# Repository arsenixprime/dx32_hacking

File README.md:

This project is focused on reverse engineering the Bridgeport DX32 CNC controller. This system uses a DOS based PC, running a custom CNC user interface applicaiton. It has an ISA card in it called the "BMDC", which has a Motorolla 68k family microcontroller on it. This card talks to two other cards via RS422 serial ports, the AUF and the TCLAuf. The AUF is used for general purpose I/O control and the TCLAuf is used for driving tool change related I/O.

Binaries provided:
* B3T.EXE - A simple system test application that exercises the functions of the BMDC board.
* BXX.EXE - The primary DX32 user interface application
* BMDC.BIN - The BMDC binary firmware, loaded by B3T or BXX when they start.
* MAINTPG.EXE - Maintenance program for viewing real-time I/O status (AUF inputs/outputs, TLAUF inputs/outputs)
* MAINTPG1.DAT - Data file for MAINTPG.EXE containing parameter bit definitions for all status/command words

More information about the BMDC board hardware. The various devices are connected via a number of programmable PALs for which the circuit diagrams are unavailable so the address mapping is unknown. The components on the board are:
* MC68EC030FE40C - Primary CPU running the firmware
* MC68882FN25A - Math coprocessor
* MAX161ACPI
* 2x ADM5180JP
* SCN2681AC1A44 - Two port async serial port

The address map is unknown

The AUF Board has:
* MC68HC811E2FN - Microcontroller
** Does have an 8ch 8bit ADC
* 4 Bit Switches for Address Select (Default 0000)
* 2x LTC485 RS422 Driver Chips
* 24x Input Channels
* 8x 24V DC Outputs. 7x Low Side. 1x High Side.
* 4x AC Outputs
* 2x LEDs, D11 and D12

## Reverse Engineering Documentation

* [PROTOCOL_NOTES.md](PROTOCOL_NOTES.md) — Master protocol document. Serial protocol between BMDC, AUF, and TLAUF (UART configuration, packet formats), ISA I/O port map, dual-port RAM layout, 68030 memory map, the TLAUF TX command protocol (VMC vs non-VMC modes), the timer/interrupt schedule (4 ms servo tick), the boot-time RAM/dual-port sizing probe, the key firmware function table, and the complete PC→BMDC mailbox command table with the DOS-side names (doMove, armProbe, wrPartPgm, ...).
* [HOMING_SEQUENCE.md](HOMING_SEQUENCE.md) — How the carousel homes on startup. Traces the full call chain from drive-ready detection through the task dispatcher to the pocket-send protocol that commands the TLAUF to move to pocket 1.
* [TOOL_CHANGE_STATE_MACHINE.md](TOOL_CHANGE_STATE_MACHINE.md) — Non-VMC tool change step machine. Documents the outer state machine (subroutine call stack) and inner step machine (carousel seek, orient, rotate) that runs when the BMDC directly controls motor outputs.
* [AUF_PACKET_FORMAT.md](AUF_PACKET_FORMAT.md) — Detailed AUF packet encoding/decoding. Covers the nibble packing for short and long packets, input debounce logic, and output bit assignments.
* [MOTION_PLANNER.md](MOTION_PLANNER.md) — How the BMDC firmware plans motion. Firmware units (10 nm, 4 ms tick), the trapezoid vs S-curve velocity planners and what parameter 010 (accel/decel profile, values 0-5) changes, when the S-curve falls back to the trapezoid, G8/G9/G99 and the P (precision) word with the corner-blending classifier, how the F word is scaled and used in combined X/Y/Z/C moves (F after a C word is the C-axis rate in deg/min, caps from parameters 7/8/47), the G117/G118/G119 rotary-coordinated moves, the move-type dispatch table, and the touch-probe engine (PC-driven via mailbox; there are no G-code probing cycles).
* [BMDC_PARAM_TABLE.md](BMDC_PARAM_TABLE.md) — All 288 firmware parameter slots (number, 68030 address, data type, title) extracted from the firmware's parameter table at 0x2a536. Use it to find where a `BMDCPRMS.SYS` parameter lives in BMDC RAM.
* [BMDC_RAM_UPGRADE.md](BMDC_RAM_UPGRADE.md) — Adding main RAM to a BMDC3 for a larger part-program buffer (the "part program memory full" alarm). Documents the fitted SRAM (MCM6226BBXJ20, 4 × 128K×8 = 512 KB), its full pin assignment, the 300-mil and 400-mil SOJ package dimensions (pitch, lead span, land pattern), the 36-lead package used by 512K×8 parts, how the firmware sizes RAM at boot and why a stock BMDC3 halts above 512 KB, the two-byte firmware patch (`tools/patch_bmdc_ram.py`), the castellated-adapter plan for 2 MB, the ISA-window test for the address decoder, and the DNC alternative.
* [BMDC_RAM_INTERPOSER_PROMPT.md](BMDC_RAM_INTERPOSER_PROMPT.md) — Ready-to-use Claude Code prompt (kicad-happy skills, KiCad 10) for designing the castellated interposer PCB that puts a 36-lead SOJ 512K×8 SRAM (CY7C1049G-10VXI) on the BMDC3's 32-lead wide SOJ site: 4-layer stack with +5 V pour over a GND plane, four 0402 decoupling caps, the host and chip pinouts, the free address/data permutation that makes it routable, a suggested net map, jumpers for A17/A18, the pad-vs-castellation clearance arithmetic, the measurements to confirm on the card, and the deliverables checklist.
* [BMDCPRMS_INI.md](BMDCPRMS_INI.md) — What each line of `BMDCPRMS.INI` does: it is a per-model override table (machine model, spindle option, 10-inch rotary table) of parameter numbers and values for `BMDCPRMS.SYS`, with the firmware address and use of every parameter it touches (travel limits, Z and C traverse caps, spindle gear-range RPMs, C-axis gains). No program in the repo reads it; its consumer is unknown.
* [BMDC3_VS_BMDC4.md](BMDC3_VS_BMDC4.md) — Every board-class branch in the firmware: how the class is decided (CPU benchmark, 1 MB + 8 KB memory fit forces BMDC4), the 68030 vs 68040 cache and FPU-software-package setup, all boot halt codes (0x90, 0xa0-0xa8, 0xb0/0xb8, 0xc0-0xe0+n), the derived hardware constants, and the runtime differences (DAC width and count, spindle DAC location and scaling, 9 vs 6 encoders, mux ADC, 16-bit input port). Includes photos of a BMDC-4B with the PWMINT daughterboard fitted and of a BMDC3S rev C without it and the assessment of running a PWMINT TC22 on a BMDC4.
* [BMDC_AXIS_OUTPUTS.md](BMDC_AXIS_OUTPUTS.md) — How the firmware chooses between the on-board analog axis DACs and the PWMINT duty-cycle card: the boot signature probe and flag 0xafc4, the halt codes 0xa1/0xa2, the PWMINT register block, the servo-tick output path and what changes between modes (centre, clamp window, gain shift, default parameter block), the PWM clamp-window maths behind parameters 124-145, why the spindle DAC is always analog, the PWMINT status/fault checks, and what happens when the card is removed.
* [BMDC_PROBE_INTERNALS.md](BMDC_PROBE_INTERNALS.md) — How touch probing works across BXX and the firmware: the PROBE ON/OFF toggle (parameter 7 plus armProbe), the overlay PROBEPT primitive, the firmware probe cycle and position latch, how SET X computes and stores work zero (the four offset copies and per-block zeros), where tool changes pass through, and the loader behaviour. Research notes for auto probe-mode and auto-zero features; nothing implemented.
* [hardware/bmdc_ram_interposer/](hardware/bmdc_ram_interposer/README.md) — The interposer itself, rev A (KiCad 10): generated 4-layer castellated board (11.83 × 27.6 mm, 32 castellations at 1.27 mm, short-pad SOJ-36 on top, four 0402 caps, JP1/JP2 solder jumpers and A17/A18 wire pads), ERC/DRC/schematic-parity clean, with gerbers/drill/CPL/BOM for JLCPCB, 3D renders, STEP, datasheets and kicad-happy analyzer reports. Everything is regenerated from `tools/params.py`; the row pitch, host pad size, chip-to-chip pitch and end clearance are still nominal and must be measured on the card before ordering.

## Mechanical Parts

* [mechanical/](mechanical/README.md) — Printed/machined hardware for the retrofit, one CadQuery generator per part with a README stating what has actually been built. Currently: [yaskawa_cord_grip/](mechanical/yaskawa_cord_grip/README.md), a split clamshell cord grip for a 3/4" knockout that passes a 0.25" and a 0.375" cable with right-angle connectors on both ends (designed, not yet printed).

## Decompiled Sources

* `decompiled/BMDC.c`, `decompiled/BXX.c`, `decompiled/B3T.c`, `decompiled/MAINTPG.c` — Ghidra decompilation of each binary, one file per binary. Grep here first rather than re-running Ghidra. `B3T.c` has real function names from the CodeView symbols.
* `decompiled/BMDC.asm` — Full Ghidra disassembly listing of the firmware. Use it whenever a `BMDC.c` function is truncated: the decompiler cannot model the 68882 `FMOVECR` / packed-decimal instructions and silently drops everything after them.
* `decompiled/B3T_symbols.txt` — CodeView symbols from `B3T.EXE` (address, kind, name, source module). The DOS-side names of the mailbox commands come from here.
* `decompiled/B3T_types.txt` — CodeView struct/union/enum records from `B3T.EXE`: the MOVEBUFFER, MOVCMD, MOVFLGS, dualPortRAM, MCCMD and parameter-block layouts shared between the DOS software and the firmware.

## Tools and Scripts

* `tools/cv_nb09.py` — Parses the CodeView NB09 debug block at the end of `B3T.EXE` and prints the symbol table (source of `decompiled/B3T_symbols.txt`).
* `tools/cv_types.py` — Dumps CodeView type records (structs, bit fields) from `B3T.EXE` by type index (source of `decompiled/B3T_types.txt`).
* `tools/m68k_dis.py` — Capstone disassembler for `BMDC.BIN` (`python3 tools/m68k_dis.py START END`) with resync after undecodable words and decoded extended-precision immediates. Needed for the mailbox, G-code-letter and move-type handlers that Ghidra never disassembled because they are only reached through jump tables.
* `tools/patch_bmdc_ram.py` — Produces a patched `BMDC.BIN` that lets a BMDC3 use more than 512 KB of RAM (`--max 1M` or `--max 16M`, `--check` to inspect an image). See `BMDC_RAM_UPGRADE.md`.
* `ghidra_scripts/ExportAllDecompiled.java` — Headless Ghidra post-script that writes every function's decompilation to one `.c` file.
* `ghidra_scripts/ExportListing.java` — Headless post-script that writes the full disassembly listing (`decompiled/BMDC.asm`).
* `ghidra_scripts/ApplyCvSymbols.java` — Applies a CSV of CodeView names (address, kind, name) to a Ghidra program before export.
* `ghidra_scripts/DisableNoReturnDiscovery.java` — Pre-script for the DOS executables. Without it Ghidra marks the Microsoft C `__chkstk` as non-returning and every function body is cut off after its first line.
* `CLAUDE.md` — Working notes for AI-assisted analysis: how to regenerate the decompiled sources with headless Ghidra, tool pitfalls, and the conventions used in the documents.

## Bench Test Scripts (no LinuxCNC needed, `pip install pyserial`)

* `dx32_proto.py` — Python reference implementation of the RS422 protocol: packet building/parsing, checksums, AUF/TLAUF bit maps.
* `test_auf.py` — Poll an AUF board over a USB-RS422 adapter and display decoded inputs; interactive output control.
* `test_tlauf.py` — Poll a TLAUF board; send VMC pocket commands.
* `test_sniff.py` — Passive bus sniffer/decoder and loopback self-test.

## LinuxCNC Integration

* [dx32_pktuart.comp](dx32_pktuart.comp) — LinuxCNC HAL component for communicating with AUF and TLAUF boards via Mesa PktUART over multidrop RS422. Supports `mode=0` (both), `mode=1` (AUF only), `mode=2` (TLAUF only) for independent testing. Build with `sudo halcompile --install dx32_pktuart.comp`.
* [LINUXCNC_COMPONENT_PROMPT.md](LINUXCNC_COMPONENT_PROMPT.md) — Full specification and design document for the PktUART component, including all HAL pin definitions, protocol details, and testing strategy.

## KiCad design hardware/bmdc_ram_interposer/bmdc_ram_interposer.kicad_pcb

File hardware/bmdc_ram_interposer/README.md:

# BMDC3 2 MB RAM interposer

Castellated 4-layer interposer that puts a 36-lead 400-mil SOJ 512K x 8 SRAM (Infineon/Cypress
**CY7C1049G-10VXI**, 5 V, 10 ns) on the 32-lead wide SOJ site of the Bridgeport BMDC3 card. Four of
them replace U8..U11 (MCM6226BBXJ20, 128K x 8) and take the card from 512 KB to 2 MB. The card is not
modified beyond swapping the chips and adding two jumper wires per interposer; the PAL address decoder
is untouched. Background: `../../BMDC_RAM_UPGRADE.md`.

Revision A, KiCad 10.0.6, 2026-10-16. **Do not order until the measurements in the first table are
confirmed on the card** (see "Regenerating").

**Status:** design complete and clean (ERC 0/0; DRC 0 violations, 0 unconnected, 0 schematic-parity
issues; fab outputs exported) but **waiting on the card measurements and meter checks** listed in
section 9 "Open items before ordering". Checklist for the bench session:

- [ ] ROW_PITCH: centre-to-centre of the two host pad rows (nominal 11.43 mm)
- [ ] host pad length (across the rows) and width (along the row), nominal 2.0 x 0.6 mm
- [ ] CHIP_PITCH: U8-U9-U10-U11 centre spacing along the row (board length 27.6 must be <= CHIP_PITCH - 0.5)
- [ ] END_CLEAR: free board area beyond each end of the 32-pad field (board overhangs it by 4.3 mm per end)
- [ ] pad 30 (E2) tied to +5 V on all four sites, or driven by 68030 A19 (decides JP1)
- [ ] pad 1 (NC) floating, or driven by 68030 A20 (decides JP2)
- [ ] where on the card 68030 A19/A20 are reachable for the two jumper wires

```
bmdc_ram_interposer.kicad_pro / .kicad_sch / .kicad_pcb   project, schematic, board
bmdc_interposer.pretty/        generated footprints (tools/gen_footprints.py)
bmdc_interposer.kicad_sym      CY7C1049G-10VXI (copied from Memory_RAM:IS61C5128AL-10KLI) and the host site symbol
tools/params.py                ALL geometry, pinouts and the net permutation (single source of truth)
tools/gen_footprints.py        footprint library generator (plain s-expressions)
tools/gen_symbols.py           symbol library generator
tools/gen_schematic.py         schematic + project file + lib tables generator
tools/build_pcb.py             board generator: placement, L1 stubs, maze router (L3/L4), zones, silk
tools/finalize_pcb.py          writes the stack-up block and plot defaults into the board
tools/export_fab.sh            gerbers, drill, CPL, BOM, renders, STEP into fab/
tools/gen_readme_tables.py     the net tables below, from params.py
datasheets/                    CY7C1049G (DigiKey API, Infineon 001-95412 Rev *F) and the 0402 capacitor
analysis/                      ERC/DRC reports and kicad-happy analyzer JSON + text reports
fab/                           fabrication outputs (regenerate with tools/export_fab.sh)
```

## 1. Measurements to confirm on the card

| name | value used | status | what it is |
|---|---|---|---|
| ROW_PITCH | 11.43 mm (450 mil) | **nominal** (user's figure) | centre-to-centre of the two host pad rows of the wide 32-pad outline |
| HOST_PAD_LEN x HOST_PAD_W | 2.0 x 0.6 mm | **nominal** | host pad size (across the row pitch x along the edge) |
| HOST_PAD_OUTER | 6.715 mm | derived | ROW_PITCH/2 + HOST_PAD_LEN/2: outer end of host pad copper from the chip centreline |
| CHIP_PITCH | unknown | **not measured** | U8/U9/U10/U11 spacing along the row of chips; board length must be <= CHIP_PITCH - 0.5 mm |
| END_CLEAR | unknown | **not measured** | free distance beyond each end of the 32-pad field; the board overhangs the pad field by 4.3 mm at each end |

Derived board size: width **11.83 mm** (ROW_PITCH + 0.4), length **27.6 mm**. The 400-mil SOJ in
`BMDC_RAM_UPGRADE.md` would give rows about 10.3 mm apart; 450 mil means the wide outline is probably
a gull-wing land, so measure it. Everything is parametric: change the values at the top of
`tools/params.py` and regenerate (section 10).

### Why 27.6 mm and not 26-27

The two solder jumpers (pads 1.0 x 1.5 mm, stock KiCad geometry) and the two wire pads must be
reachable with the SRAM fitted, so they sit in the strips beyond the SRAM body ends together with the
decoupling capacitors. The strip needs 1.6 mm (body end 11.81 + 0.1, jumper pad 1.5, 0.25 to the
edge), which sets the minimum length at 27.4 mm; 27.6 mm adds 0.1 mm per end of margin. If
CHIP_PITCH - 0.5 turns out smaller than 27.4 mm, the fallback the brief allows is to move the caps
(and, here, the jumpers) under the SRAM body between the pad rows (SOJ standoff 0.64 mm minimum, an
0402 is 0.5 mm tall) and keep only the wire pads in the end strips, which then need 1.1 mm (board
>= 26.0 mm). That variant is **not implemented in rev A**: it needs new placements in
`tools/build_pcb.py` (the router and footprints need no change). Below 26.0 mm the wire pads have
no accessible place and the design needs rethinking (e.g. flying leads from the castellations).

## 2. Host <-> SRAM net assignment

Net names are the **host** signal names. Address lines and data lines are permuted (the SRAM does not
care which host address bit drives which pin as long as reads and writes see the same mapping, which
they do); controls and power are not. The permutation was chosen so that, on each edge, every group
of nets that shares a routing layer is monotone (no crossings), which is what makes the board
routable with no vias other than the fan-out vias. Generated by `tools/gen_readme_tables.py`; the
schematic carries the same labels.

| host pin | host signal | net | SRAM pin (name) | edge / note |
|---|---|---|---|---|
| 1 | NC | HOST_PIN1 | - | A: JP2 (open) to A18; nothing else |
| 2 | A16 | A16 | 33 (A16) | A: crosses the board |
| 3 | A14 | A14 | 1 (A0) | A: same edge |
| 4 | A12 | A12 | 2 (A1) | A: same edge |
| 5 | A7 | A7 | 3 (A2) | A: same edge |
| 6 | A6 | A6 | 4 (A3) | A: same edge |
| 7 | A5 | A5 | 5 (A4) | A: same edge |
| 8 | A4 | A4 | 14 (A5) | A: same edge |
| 9 | A3 | A3 | 15 (A6) | A: same edge |
| 10 | A2 | A2 | 16 (A7) | A: same edge |
| 11 | A1 | A1 | 17 (A8) | A: same edge |
| 12 | A0 | A0 | 18 (A9) | A: same edge |
| 13 | DQ0 | DQ0 | 8 (I/O1) | A: same edge |
| 14 | DQ1 | DQ1 | 11 (I/O2) | A: same edge |
| 15 | DQ2 | DQ2 | 12 (I/O3) | A: same edge |
| 16 | VSS | GND | 10 (GND), 28 (GND) | A: L2 plane, SRAM 10 and 28, C1-C4 |
| 17 | DQ3 | DQ3 | 7 (I/O0) | B: crosses the board |
| 18 | DQ4 | DQ4 | 25 (I/O4) | B: same edge |
| 19 | DQ5 | DQ5 | 26 (I/O5) | B: same edge |
| 20 | DQ6 | DQ6 | 29 (I/O6) | B: same edge |
| 21 | DQ7 | DQ7 | 30 (I/O7) | B: same edge |
| 22 | ~{E1} | ~{CE1} | 6 (~{CE}) | B: crosses the board |
| 23 | A10 | A10 | 20 (A10) | B: same edge |
| 24 | ~{G} | ~{OE} | 31 (~{OE}) | B: same edge |
| 25 | A11 | A11 | 21 (A11) | B: same edge |
| 26 | A9 | A9 | 22 (A12) | B: same edge |
| 27 | A8 | A8 | 23 (A13) | B: same edge |
| 28 | A13 | A13 | 24 (A14) | B: same edge |
| 29 | ~{W} | ~{WE} | 13 (~{WE}) | B: crosses the board |
| 30 | E2 | E2 | - | B: JP1 (open) to A17; nothing else |
| 31 | A15 | A15 | 32 (A15) | B: same edge |
| 32 | VCC | +5V | 9 (VCC), 27 (VCC) | B: L1 pour, SRAM 9 and 27, C1-C4 |

| SRAM pin | SRAM name | net | from |
|---|---|---|---|
| 1 | A0 | A14 | host 3 (A14) |
| 2 | A1 | A12 | host 4 (A12) |
| 3 | A2 | A7 | host 5 (A7) |
| 4 | A3 | A6 | host 6 (A6) |
| 5 | A4 | A5 | host 7 (A5) |
| 6 | ~{CE} | ~{CE1} | host 22 (~{E1}) |
| 7 | I/O0 | DQ3 | host 17 (DQ3) |
| 8 | I/O1 | DQ0 | host 13 (DQ0) |
| 9 | VCC | +5V | host 32 (VCC) |
| 10 | GND | GND | host 16 (VSS) |
| 11 | I/O2 | DQ1 | host 14 (DQ1) |
| 12 | I/O3 | DQ2 | host 15 (DQ2) |
| 13 | ~{WE} | ~{WE} | host 29 (~{W}) |
| 14 | A5 | A4 | host 8 (A4) |
| 15 | A6 | A3 | host 9 (A3) |
| 16 | A7 | A2 | host 10 (A2) |
| 17 | A8 | A1 | host 11 (A1) |
| 18 | A9 | A0 | host 12 (A0) |
| 19 | NC | NC | no connection |
| 20 | A10 | A10 | host 23 (A10) |
| 21 | A11 | A11 | host 25 (A11) |
| 22 | A12 | A9 | host 26 (A9) |
| 23 | A13 | A8 | host 27 (A8) |
| 24 | A14 | A13 | host 28 (A13) |
| 25 | I/O4 | DQ4 | host 18 (DQ4) |
| 26 | I/O5 | DQ5 | host 19 (DQ5) |
| 27 | VCC | +5V | host 32 (VCC) |
| 28 | GND | GND | host 16 (VSS) |
| 29 | I/O6 | DQ6 | host 20 (DQ6) |
| 30 | I/O7 | DQ7 | host 21 (DQ7) |
| 31 | ~{OE} | ~{OE} | host 24 (~{G}) |
| 32 | A15 | A15 | host 31 (A15) |
| 33 | A16 | A16 | host 2 (A16) |
| 34 | A17 | A17 | TP1 wire pad (68030 A19); JP1 to host 30 |
| 35 | A18 | A18 | TP2 wire pad (68030 A20); JP2 to host 1 |
| 36 | NC | NC | no connection |

Four nets cross the board: host 2 (A16) to SRAM pin 33 at the pin-1 end, host 17 (DQ3) to SRAM pin 7,
and the two controls ~E1 -> ~CE and ~W -> ~WE, which are fixed by function.

## 3. Jumper and wire-pad policy (A17/A18 = 68030 A19/A20)

The two extra address bits of a 512K x 8 part must come from 68030 **A19 and A20**, which do not
reach the SOJ site unless the card happens to route them to pads 30 and 1.

* **TP1 (A17)** and **TP2 (A18)** are 1.5 x 1.0 mm wire pads on L1 at the far (+Y, pin-18/19) end.
  Run 30 AWG wire from them to 68030 A19 (TP1) and A20 (TP2) on the card. All four interposers are
  bussed to the same two CPU pins.
* **JP1** bridges A17 to castellation 30 (host pin 30, today E2). **JP2** bridges A18 to castellation 1
  (host pin 1, today NC). Both are **open by default** and sit at the pin-1 (-Y) end. Castellations 1
  and 30 have no other connection, so with the jumpers open those two host pads are electrically
  unused by the interposer.
* Close a jumper only after verifying with a meter, chips removed, that the card drives 68030
  A19/A20 on that pad. Whether A19/A20 are decoded at all is decided by the ISA-window aliasing test
  in `BMDC_RAM_UPGRADE.md` (write through the dual-port window at an address and at the same address
  + 512 KB with the original chips fitted; if they alias, the PAL ignores A19 and the extra bits are
  simply unused above the first 512 KB word of each bank until the jumper wires are added).

**E2 assumption and risk.** Host pin 30 is E2, the active-HIGH chip enable of the MCM6226. The design
assumes the card ties it high (the MCM6226 datasheet treats E1/E2 as one enable of opposite
polarity, and the pad is unused by the 36-SOJ part). If pin 30 turns out to be a decode term from
the PAL (E2 driven per bank), the CY7C1049G has no second enable to receive it and the interposer
would need an extra gate (~CE = ~E1 OR ~E2) - out of scope for this board. Check with a meter that
pin 30 sits at +5 V on all four sites before relying on ~E1 alone.

## 4. Layout

Coordinates: origin at the SRAM centre, X across the board (edge A at -X carries host pins 1-16, edge
B at +X carries 17-32), Y along the board (pin 1 end at -Y).

| layer | content |
|---|---|
| L1 F.Cu | SRAM (custom short-pad SOJ-36), C1-C4, JP1/JP2, TP1/TP2, solid +5 V pour, 0.2 mm stubs from every SRAM signal pad inward to a fan-out via at X = +-1.905 mm (no via-in-pad) |
| L2 In1.Cu (named GND_L2, power layer) | unbroken GND plane, solid for X within +-5.165; connects castellation 16 (via at -2.54, 8.89), SRAM 10/28 (through their fan-out vias), C1-C4 GND pads (shared via per end, 0.82 mm from each pad centre) |
| L3 In2.Cu | signal routing: castellation entries come straight out of the plated half-hole (1.1 mm ring, track end inside it at X = 5.461), then run in the 1.9 mm channel between the castellations and the via column, or through the central strip |
| L4 B.Cu | castellation lands (1.2 mm inward reach) and the rest of the signal routing. Nothing mounted, no silk; everything but the lands is under solder mask |

Castellations: 32 plated 0.6 mm holes centred exactly on the long board edges, 1.27 mm pitch, 16 per
edge, 19.05 mm first-to-last, numbered 1..16 down edge A and 17..32 back up edge B (32 opposite 1).
Each is a KiCad pad with the *castellated* property and a per-layer pad stack: 1.0 mm circle on L1
(0.2 mm ring), 1.1 mm circle on L2 and L3 (0.25 mm ring; the 32 idle L2 rings are half outside the
board and the plane keeps 0.2 mm from them), and a 1.7 x 1.0 mm land on L4 shifted 0.35 mm inward
(copper 1.2 mm inside the edge, 0.5 mm outside the edge is milled away). KiCad's "remove unused
layers" is deliberately not used: KiCad 10 drops the L3 ring even when a trace ends inside it.
Castellations 16 (GND) and 32 (+5 V) have solid zone connection; both also reach their plane/pour
through a dedicated via next to the pad row (GND at -2.54, 8.89; +5 V at 2.54, -8.89).

Fan-out: the via column sits 1.905 mm from the centreline, 1.9 mm inboard of the SRAM pad ends.
Earlier revisions of the generator put it at 3.05 mm; that leaves only a 3-track channel per layer
between the vias and the castellations, and the groups host 8-12 -> SRAM 14-18 are pairwise
overlapping on one side of the column, which cannot be routed on two layers without a via per net.
At 1.905 mm each edge has a 6-track two-sided channel per layer plus a free central strip, and every
net routes with zero extra vias. The +5 V pour on L1 is consequently a comb under the SRAM (fingers
between the stubs, a 2.8 mm solid centre strip) and solid elsewhere; it feeds SRAM 9/27 directly and
castellation 32 through a via at (2.54, -8.89).

Router: `tools/build_pcb.py` contains a small grid (0.127 mm) maze router with negotiated-congestion
re-routing; fixed copper (pads, stubs, lands, rings) is a hard obstacle with the clearances below,
other nets' traces are soft obstacles whose penalty grows each pass. It converged with zero conflicts
for this geometry. It is deterministic (seeded), so a regenerate reproduces the same board.

Silkscreen (L1): U1 reference and "BMDC3 2MB rev A" under the SRAM body (visible before the chip is
fitted), JP1/JP2 and A17/A18 labels just inside the body ends next to the parts they name, SRAM pin-1
triangle beside pad 1, castellation-1 marker dot in the pin-1 corner of the board.

## 5. Clearance arithmetic (ROW_PITCH = 11.43, board width 11.83)

* Hole centre at X = +-5.915. Hole radius 0.3, L1 ring 0.2 -> L1 ring copper reaches inward to
  **5.415** (inner-layer rings 1.1 mm reach 5.365; those layers carry no SRAM pads; ring to ring
  along the edge 1.27 - 1.1 = 0.17 >= 0.15).
* SRAM pads: 1.365 x 0.6 mm at X = +-4.4825, copper from **3.8 to 5.165**. Ring to pad gap =
  5.415 - 5.165 = **0.25 mm** (>= 0.2 required; JLCPCB minimum 0.09). The J-lead contact point is at
  +-4.7 (contact span 0.360-0.380 in = 9.14-9.65 mm per datasheet drawing 51-85090), i.e. 0.47 mm
  inside the pad end with 0.9 mm of pad under the lead; the stock KiCad SOJ-36 pads (3.875-6.025)
  would overlap the rings.
* Solder mask: expansion 0 (KiCad default, JLCPCB applies 1:1), so the mask web between a ring
  opening and the neighbouring pad opening is the full 0.25 mm (>= 0.1 required).
* Hole to hole along the edge: 1.27 - 0.6 = 0.67 mm (JLCPCB >= 0.5 for castellations); hole to the
  short board edges: 3.9 mm (>= 1 mm).
* Castellation L4 lands: 1.0 mm wide at 1.27 pitch -> 0.27 mm copper gap and 0.27 mm mask web.
* Design rules: track 0.2 mm, clearance 0.15 mm (DRC net class), via 0.6/0.3 mm, copper to edge
  0.25 mm (castellated pads exempt), hole to copper 0.25 mm, zone clearance 0.2 mm, zone min width
  0.25 mm, thermal reliefs 0.3 spoke / 0.2 gap (cap +5 V pads and SRAM power pads solid).
* If the measured ROW_PITCH lets the board be wider, `CHIP_PAD_OUTER_X` in `params.py` grows
  automatically (it is min(6.025, ring inner X - 0.25)).

## 6. Stack-up and fab options (JLCPCB; PCBWay equivalent)

| option | value |
|---|---|
| layers / thickness | 4 / **1.0 mm** (card + interposer + SOJ must clear the neighbouring ISA slot) |
| stack-up | **JLC04101H-3313**: 1 oz outer copper, 3313 prepreg (about 0.1 mm, Er 4.1) between L1 (+5 V) and L2 (GND) for maximum interplane capacitance, 0.5 oz inner copper, core about 0.58 mm. (JLC04161H-3313 in the brief is the same family at 1.6 mm.) Fallback: the standard 7628 stack if 3313 is not offered for 1.0 mm. |
| finish | **ENIG** (castellations and the 1.27 mm pitch pads solder better than with HASL) |
| castellated holes | **yes - tick "Castellated holes" in the order**, 0.6 mm, on the two long edges |
| panel | none required; if JLCPCB panelises, mouse-bites on the short ends only, no V-score |
| mask / silk | green, white silk top only; "remove order number: specify a location" (there is no free silk area; let them put it on L4, which is hidden against the card) |
| quantity | 5 minimum; you need 4 |

The gerber set in `fab/` was exported with Protel extensions, mask subtracted from silk, Excellon
drill (decimal, mm, absolute origin) with a Gerber X2 drill map, plus a JLCPCB-format CPL and BOM.

## 7. BOM

| ref | qty/board | part | MPN | notes |
|---|---|---|---|---|
| U1 | 1 | 512K x 8 SRAM, 5 V, 10 ns, 36-SOJ | **CY7C1049G-10VXI** (Infineon/Cypress), DigiKey CY7C1049G-10VXI-ND | datasheet 001-95412 Rev *F; pinout verified against Figure 1, package 51-85090 |
| C1-C4 | 4 | 100 nF 16 V X7R 0402 | **CL05B104KO5NNNC** (Samsung), LCSC C1525 (JLCPCB basic part), DigiKey 1276-1004-1-ND | any 0402 X7R 100 nF >= 16 V works (Murata GRM155R71C104KA88D, etc.). Note: the file DigiKey served into `datasheets/` is Samsung's generic CL05 spec (named for the Y5V sibling CL05F104ZO5NNNC); CL05**B** is the X7R code |
| JP1, JP2 | 2 | solder jumper, open | - | no part |
| TP1, TP2 | 2 | wire pad | - | no part; 30 AWG wire-wrap wire to 68030 A19/A20 |
| J1 | 1 | castellated host interface | - | the board edge itself |

Four interposers: 4 x CY7C1049G-10VXI, 16 x 0402 capacitors.

## 8. Assembly order

1. Reflow or hot-air the SRAM and the four capacitors onto the interposer first (top side only; the
   bottom is flat). Check the SRAM pin 1 (silk triangle beside pad 1, chamfered corner on the fab
   outline) is at the end with the castellation-1 dot and JP1/JP2.
2. Decide the jumpers (section 3) while the card is still fitted with its original chips, then
   remove U8..U11 from the card and clean the pads.
3. Solder the interposers to the card by hand with the card flat: tack castellation 1 and 32, check
   the half-holes sit on the outer half of the host pads with copper visible outside the board edge,
   then run the remaining 30 castellations with a fine tip and flux. Pin 1 of the interposer (dot
   and chamfer) goes to pin 1 of the site (the end marked on the card's silk outline).
4. Run the wires from TP1/TP2 of all four interposers to 68030 A19/A20.
5. Patch the firmware before the card will boot with more than 512 KB:
   `python3 tools/patch_bmdc_ram.py --max 16M` (repository root), background in `BMDC_RAM_UPGRADE.md`.

## 9. Verification

All checks below were run on the files in this directory as delivered (KiCad 10.0.6 `kicad-cli`,
kicad-happy 1.3.1 analyzers). Reports are in `analysis/`.

| check | result |
|---|---|
| `kicad-cli sch erc --severity-all` | **0 errors, 0 warnings** (`analysis/erc.rpt`) |
| `kicad-cli pcb drc --severity-all --schematic-parity` | **0 violations, 0 unconnected items, 0 schematic-parity issues** (`analysis/drc.rpt`, `drc.json`) |
| routing | 34 nets, 426 track segments, 54 vias (0.6/0.3), all nets complete; router converged with 0 conflicts |
| `analyze_schematic.py` | 0 errors, 1 warning (RS-001 "+5V has no declared source": it is the host card, through castellation 32) |
| `analyze_pcb.py --full` | 4 "errors", 6 warnings, all PM-002 edge-distance and TE-001 (see below); routing_complete true |
| `cross_analysis.py` | 9 findings: RP-002 x8 and PS-002 (see below) |
| `analyze_emc.py` | GP-001 / RP-001 / SU-001 / DC-002 (see below); no other rule fired |
| `analyze_thermal.py` | nothing to report (45 mA part) |
| `analyze_gerbers.py` | 0 errors, 1 warning (GR-004 paste coverage 32%: only U1 and C1-C4 have paste; castellations, jumpers and wire pads deliberately have none); all 9 expected layers present, drill file complete, 54 x 0.3 mm vias + 32 x 0.6 mm castellation holes, outline closed, 11.93 x 27.7 mm bounding box (outline line width included) |
| SPICE | not applicable: no analog subcircuits |

Explained analyzer findings (none of them are design defects for this board):

* **PM-002 "JP1/JP2 0.15 mm, TP1/TP2 0.4 mm, C1-C4 0.54 mm from board edge"**: courtyard-to-edge
  distances. The brief puts these parts in the 1.6 mm strips beyond the SRAM body; copper to edge is
  0.25 mm (JLCPCB minimum 0.2), checked by DRC.
* **GP-001 / SU-001 "reference plane gap", "adjacent signal layers"**: the brief's stack-up is
  SIG-GND-SIG-SIG. Traces on L4 reference the GND plane through the core (~0.8 mm away) and L3
  through 0.1 mm of prepreg; that is the chosen trade-off (thin L1-L2 prepreg for the +5 V / GND
  interplane capacitance). At 40 MHz bus rate and 10 ns edges over <= 25 mm this has no effect.
* **RP-002 / PS-002 "signals cross a GND plane gap", "plane split: 7 islands"**: the GND plane is a
  single polygon (252 mm2, 78% of the board) that stops 0.2 mm short of the castellation rings; the
  L3 entry traces run 0.3 mm over that edge strip. The analyzer's island count comes from its own
  connectivity graph treating the 32 half-hole rings on L2 as plane pieces.
* **RP-001 "missing stitching via at layer transition"**: the only layer transitions are the fan-out
  vias next to the SRAM pads and the entries; there is no room for a GND via per signal, and the
  plane is 0.1 mm away on L1's side.
* **DC-002 "no decoupling cap near U1"**: the caps are in the end strips (brief requirement), 2 mm
  from the SRAM body ends; the +5 V / GND plane pair under the chip is the high-frequency path.
* **TB-001 tombstoning risk (info)**: the cap GND pads go to a shared via through a short stub, the
  +5 V pads sit in the solid pour (solid connection, no thermal relief, because the end strip is too
  narrow for two spokes). Hot-air or reflow with a stencil; do not drag-solder the caps.
* **TE-001 / FD-001 / EP-AUD / IO-00x** (test points, fiducials, ESD, connector filtering): not
  applicable to a 11 x 28 mm interposer inside an ISA card.

### Acceptance checklist (from the brief)

- [x] ERC 0 errors, DRC 0 errors (0 warnings as well; analyzer warnings explained above)
- [x] analyze_schematic.py, analyze_pcb.py, cross_analysis.py, analyze_gerbers.py run; no single-pin nets, no unconnected pads except castellations 1 and 30 (JP2/JP1 open) and SRAM NC pins 19/36
- [x] every castellation 1-32 present, numbered 1 opposite 32, 1.27 mm pitch, 19.05 mm first-to-last (`BMDC3_SOJ32_Castellated`)
- [x] 36 SRAM pads, custom shortened footprint, 0.25 mm from every foreign-net castellation ring on L1
- [x] L2 unbroken GND plane; L1 +5 V pour connected to castellation 32 (via at 2.54, -8.89) and both VCC pins (solid connection)
- [x] four 0402 caps, two per end, each GND pad 0.82 mm from the shared L2 via at that end
- [x] address/data permutation table generated from the same file as the schematic labels
- [ ] board length <= CHIP_PITCH - 0.5 mm, width = ROW_PITCH + 0.4 **- waits for the measurements**
- [x] fab export against the JLCPCB rules in the `jlcpcb` skill (4-layer: 0.09 mm trace/space minimum vs 0.2/0.15 used, via 0.25/0.15 minimum vs 0.6/0.3, castellated hole >= 0.5 mm vs 0.6, hole-to-hole >= 0.5 vs 0.67, copper to edge >= 0.2 vs 0.25, silk >= 0.15 mm lines / 0.8 mm text) - tick "castellated holes" when ordering

### Open items before ordering

1. Measure ROW_PITCH, host pad size, CHIP_PITCH and END_CLEAR on the card; put them in
   `tools/params.py`; regenerate; re-run ERC/DRC and `tools/export_fab.sh`.
2. Meter check on the card: pin 30 (E2) tied to +5 V on all four sites; whether 68030 A19/A20 reach
   pads 30/1 (decides JP1/JP2).
3. The 36-SOJ J-leads overhang the castellation rings by ~0.5 mm at the outer bend; the rings are
   exposed copper 0.25 mm outside the pads under a mask dam. Solder the SRAM with a stencil-sized
   paste deposit on the pads only; excess paste can bridge the fillet to the ring.

## 10. Regenerating

```bash
cd hardware/bmdc_ram_interposer
# edit tools/params.py (measured ROW_PITCH, HOST_PAD_*, CHIP_PITCH, END_CLEAR, BOARD_LEN ...)
python3 tools/gen_footprints.py            # bmdc_interposer.pretty/
python3 tools/gen_symbols.py               # bmdc_interposer.kicad_sym
python3 tools/gen_schematic.py             # .kicad_sch, .kicad_pro, lib tables
python3 tools/build_pcb.py                 # .kicad_pcb (3-4 minutes, prints routing passes)
python3 tools/finalize_pcb.py              # stack-up block
kicad-cli sch erc --severity-all -o analysis/erc.rpt bmdc_ram_interposer.kicad_sch
kicad-cli pcb drc --severity-all --schematic-parity -o analysis/drc.rpt bmdc_ram_interposer.kicad_pcb
tools/export_fab.sh                        # fab/
```

The generators need KiCad 10 (`kicad-cli`, the `pcbnew` Python module) and numpy. The board is
rebuilt from scratch each time; hand edits to the .kicad_pcb are lost, so put changes into the
generators. Routing is deterministic for a given geometry.

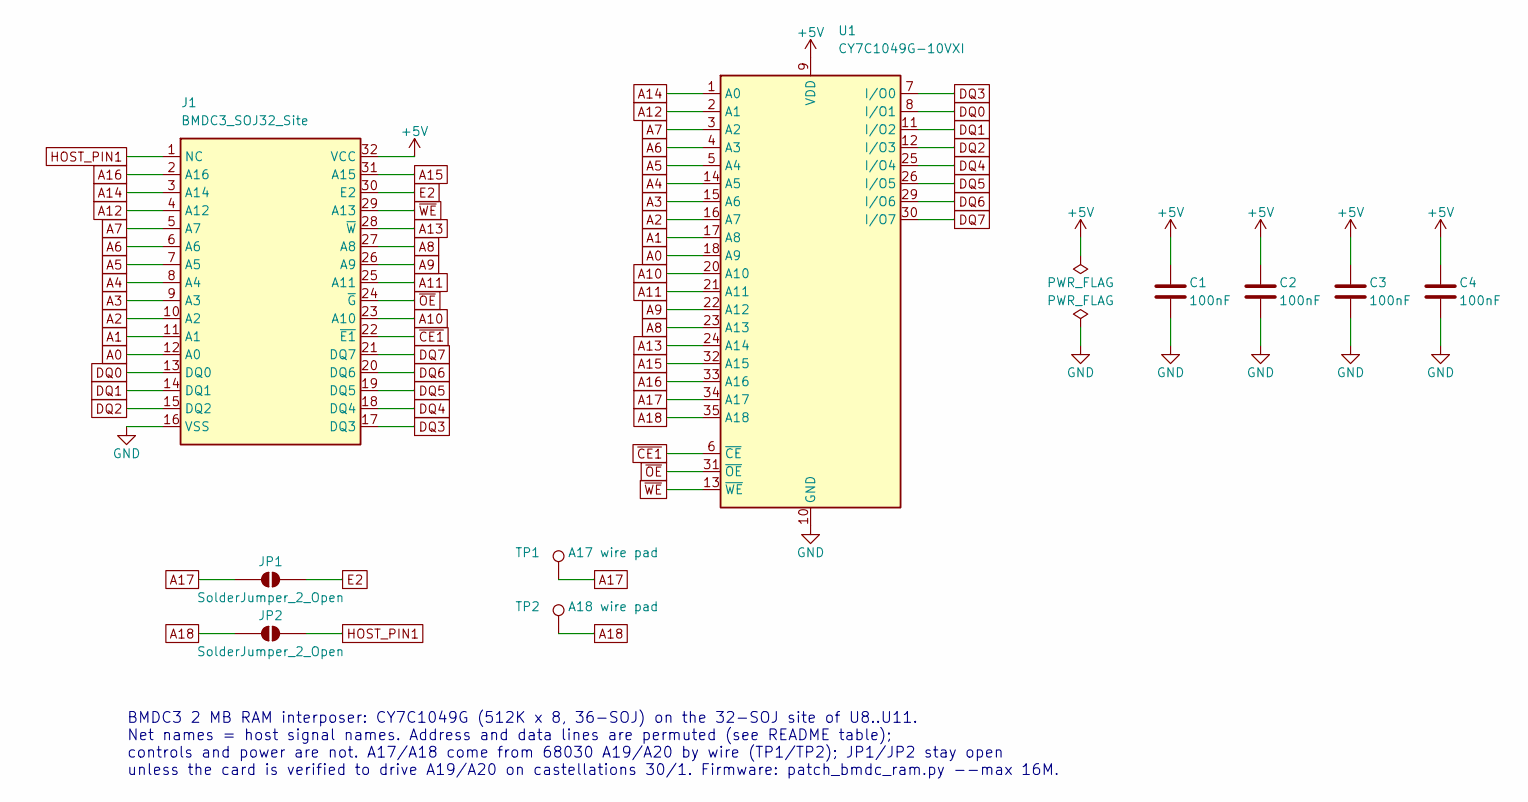
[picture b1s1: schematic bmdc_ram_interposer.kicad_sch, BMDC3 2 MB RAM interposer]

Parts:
C1, C2, C3, C4: 100nF; C_0402_1005Metric; MPN CL05B104KO5NNNC; LCSC C1525
J1: BMDC3_SOJ32_Site; BMDC3_SOJ32_Castellated
JP1, JP2: SolderJumper_2_Open; SolderJumper-2_P1.3mm_Open_Pad1.0x1.5mm
TP1: A17 wire pad; WirePad_1.5x1.0mm
TP2: A18 wire pad; WirePad_1.5x1.0mm
U1: CY7C1049G-10VXI; SOJ-36_10.16x23.495mm_P1.27mm_ShortPads; MPN CY7C1049G-10VXI; DigiKey CY7C1049G-10VXI-ND

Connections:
+5V: C1.1, C2.1, C3.1, C4.1, J1.32 (VCC), U1.9 (VDD), U1.27 (VDD)
A0: J1.12 (A0), U1.18 (A9)
A1: J1.11 (A1), U1.17 (A8)
A2: J1.10 (A2), U1.16 (A7)
A3: J1.9 (A3), U1.15 (A6)
A4: J1.8 (A4), U1.14 (A5)
A5: J1.7 (A5), U1.5 (A4)
A6: J1.6 (A6), U1.4 (A3)
A7: J1.5 (A7), U1.3 (A2)
A8: J1.27 (A8), U1.23 (A13)
A9: J1.26 (A9), U1.22 (A12)
A10: J1.23 (A10), U1.20 (A10)
A11: J1.25 (A11), U1.21 (A11)
A12: J1.4 (A12), U1.2 (A1)
A13: J1.28 (~W), U1.24 (A14)
A14: J1.3 (A14), U1.1 (A0)
A15: J1.31 (A15), U1.32 (A15)
A16: J1.2 (A16), U1.33 (A16)
A17: JP1.1 (A), TP1.1, U1.34 (A17)
A18: JP2.1 (A), TP2.1, U1.35 (A18)
DQ0: J1.13 (DQ0), U1.8 (I/O1)
DQ1: J1.14 (DQ1), U1.11 (I/O2)
DQ2: J1.15 (DQ2), U1.12 (I/O3)
DQ3: J1.17 (DQ3), U1.7 (I/O0)
DQ4: J1.18 (DQ4), U1.25 (I/O4)
DQ5: J1.19 (DQ5), U1.26 (I/O5)
DQ6: J1.20 (DQ6), U1.29 (I/O6)
DQ7: J1.21 (DQ7), U1.30 (I/O7)
E2: J1.30 (E2), JP1.2 (B)
GND: C1.2, C2.2, C3.2, C4.2, J1.16 (VSS), U1.10 (GND), U1.28 (GND)
HOST_PIN1: J1.1 (NC), JP2.2 (B)
~CE1: J1.22 (~E1), U1.6 (~CE)
~OE: J1.24 (~G), U1.31 (~OE)
~WE: J1.29 (A13), U1.13 (~WE)

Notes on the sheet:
BMDC3 2 MB RAM interposer: CY7C1049G (512K x 8, 36-SOJ) on the 32-SOJ site of U8..U11. Net names = host signal names. Address and data lines are permuted (see README table); controls and power are not. A17/A18 come from 68030 A19/A20 by wire (TP1/TP2); JP1/JP2 stay open unless the card is verified 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

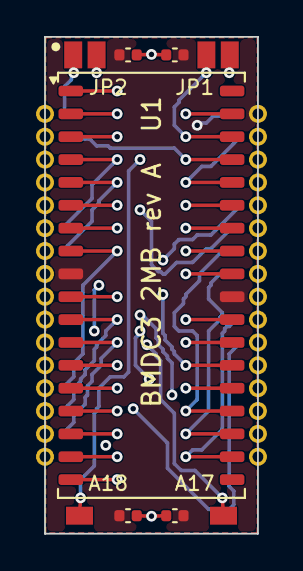
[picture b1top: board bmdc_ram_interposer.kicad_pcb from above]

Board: 4 copper layers, 11.8 x 27.6 mm, 10 parts (0 on the bottom side), 34 nets.

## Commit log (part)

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2026-04-11 initial commit. initial results.
2026-04-11 major update. tool change logic now figured out. updated docs.
2026-04-12 added python test script for AUF/TLAUF communication
